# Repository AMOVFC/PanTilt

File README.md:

# Motorized 4-Axis Camera Slider — ESP32-S3

DIY motorized camera slider built around a salvaged 2020 aluminium V-slot
extrusion. Four motorized axes, live knob control, and a programmed keyframe
system for smooth multi-axis cinematic moves. The camera is a phone running the
Blackmagic Camera app; recording is triggered wirelessly over BLE HID.

## Axes

| Axis | Drive | Reduction | Position sensing |
|---|---|---|---|
| Slide | GT2 belt along the 2020 rail, V-wheel carriage | 1:1 | 2× limit switches (min/max) |
| Pan | 2-stage GT2 belt (20T:20T jackshaft, then 20T:80T) | 4:1 | AS5600 absolute encoder — no homing |
| Tilt | Same 2-stage scheme as pan | 4:1 | AS5600 absolute encoder — no homing |
| Z (height) | Integrated leadscrew NEMA 17, anti-backlash nut | 8 mm lead | 1× limit switch, then step-counted |

Pan and tilt read absolute angle on every power-up, so they never need a homing
move. Slide and Z home against physical switches.

## Where things live

| Path | What it is |
|---|---|
| **[`hardware/`](hardware/)** | The production PCB — `pantilt-controller`, a KiCad 10 project. Carrier for an ESP32-S3 DevKitC-1 + 4× TMC2209 sockets + I²C mux + encoders + OLED, with fused inputs and TVS protection on the 24 V / 5 V rails. Board renders, full BOM with LCSC part numbers, and the DFM review scripts are in there. |
| **[`software/`](software/)** | The firmware — a PlatformIO project for the ESP32-S3. Motion, TMC2209 UART control, encoders, sequencer, and a self-hosted web UI. Build and flash from inside `software/`. |
| **[`legacy/`](legacy/)** | Every earlier design generation — nothing the current firmware or board depends on. |

### Legacy generations

| Variant | Path | Why it stopped |
|---|---|---|
| Prototype | [`legacy/prototype/`](legacy/prototype/README.md) | 3-axis hand-wired origin of the project, with its own firmware |
| Integrated | [`legacy/integrated/`](legacy/integrated/README.md) | everything soldered incl. 4× QFN28; never routed |
| Hybrid | [`legacy/hybrid/`](legacy/hybrid/README.md) | soldered MCU + power, plug-in drivers |
| Turnkey / -mini / full / pwr | [`legacy/pantiltslide/`](legacy/pantiltslide/README.md) | earlier carrier boards; `hardware/pantilt-controller` descends from turnkey-mini |
| TMC socket generator | [`legacy/tmc2209-socket-gen/`](legacy/tmc2209-socket-gen/) | script + library for the custom TMC2209 socket footprint |

## The board in one paragraph

An ESP32-S3 DevKitC-1 drops into two 22-pin sockets. Four TMC2209
SilentStepSticks and a TCA9548A breakout plug into pin sockets; two AS5600
encoder heads, four panel encoders, four buttons and the limit switches plug in
over JST-XH; the OLED and the six spare mux channels break out on 1×4 pin
headers. Both supply rails are fused — a 4 A MINI blade fuse on the 24 V motor
rail, a 1.5 A Nano² on the 5 V logic rail — with a TVS crowbar downstream of
each fuse and a bleeder across the 24 V bulk caps so hand-driving an axis while
the board is off can't leave the capacitors charged. Details and BOM:
[`hardware/README.md`](hardware/README.md).

## The firmware in one paragraph

Motion runs on STEP/DIR through FastAccelStepper; the TMC2209s are configured
and health-checked over one shared half-duplex UART, so run current and
microstepping are set by firmware rather than by trimpots and jumpers. Anything
machine-specific — pin map, mechanics, speeds, soft limits, control bindings,
network — is runtime config on the ESP32's filesystem, edited from a web UI
that is compiled into the image. `software/include/config.h` holds factory
defaults only. Bring-up order and bench notes:
[`software/docs/firmware.md`](software/docs/firmware.md).

## Manufacturing

PCBWay fabricate the bare 4-layer PCB. Components are **hand-assembled** —
PCBWay only warranty parts they also place, so the BOM is kept to common,
reusable Uniroyal / Yageo passives and widely-stocked LCSC parts. Motors, PSU,
AS5600 modules, OLED, encoders and mechanical parts wire in over connectors.

## Quick start

```bash
cd software
pio run -t upload && pio device monitor
```

Flash through the DevKitC-1's **`UART`** USB socket (not `USB`). The board then
comes up as a WiFi AP — SSID `CamSlider`, password `sliderpad`, UI at
`http://192.168.4.1`. Full instructions and the mandatory pre-motor bring-up
sequence: [`software/README.md`](software/README.md).

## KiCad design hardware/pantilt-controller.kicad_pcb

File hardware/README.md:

# pantilt-controller — carrier board

The production PCB for the 4-axis camera slider. A carrier for an **ESP32-S3
DevKitC-1** that fans the module out to four **TMC2209 SilentStepStick** driver
sockets, a **TCA9548A** I²C mux, two **AS5600** encoder heads, an OLED, four
quadrature encoders, four buttons and the limit switches — everything on
plug-in connectors — plus on-board power protection on the 24 V and 5 V rails.

Everything that describes a *particular* machine (pin map, mechanics, speeds,
limits) lives in the firmware's runtime config, not on this board. See
[`../software/`](../software/).

|  |  |
|---|---|
|  |  |
| **Top** — every cabled connector (JST-XH, terminal blocks, 1×4 headers for the OLED and spare mux channels), the electrolytics, F1 / F2 and the power LEDs | **Bottom** — the DevKit, TMC2209 and TCA9548A sockets (the modules plug in from underneath), SMD decoupling, I²C pull-ups, TVS diodes |

Renders are `kicad-cli` ray-traces of the board file. F1 and F2 have no 3-D
model and show as bare pads. To regenerate, from this folder:

```bash
kicad-cli pcb render --side top    --rotate "-40,0,35"  --zoom 0.9 --quality high --floor --perspective --background opaque --width 1568 --height 984 --output renders/pantilt-controller-top.png    pantilt-controller.kicad_pcb
kicad-cli pcb render --side bottom --rotate "-40,0,-35" --zoom 0.9 --quality high --floor --perspective --background opaque --width 1568 --height 984 --output renders/pantilt-controller-bottom.png pantilt-controller.kicad_pcb
```

## At a glance

| | |
|---|---|
| Size | 52.3 × 93.2 mm |
| Layers | 4 (1 oz outer + inner) |
| Stackup | `F.Cu` / prepreg 0.1 / `In1.Cu` / core 1.24 / `In2.Cu` / prepreg 0.1 / `B.Cu` ≈ 1.6 mm |
| Planes | `In1.Cu` + `In2.Cu` are both solid GND; F/B carry signal + power |
| Rails | 24 V (motor), 5 V (DevKit + logic), 3.3 V (from the DevKit regulator) |
| DRC | 0 errors, 0 unconnected · 64 warnings, all cosmetic (silkscreen overlap / silk over copper, back-layer text, TMC socket library-copy mismatch) |
| ERC | 0 errors · 96 warnings, mostly off-grid wire endpoints |
| Schematic parity | 30 items — 26 part-field syncs (MPN / LCSC / Notes not yet copied onto the footprints; *Update PCB from Schematic* fixes them without moving anything, since every symbol's footprint matches the board) plus 4 notes on the unnamed `REF**` mounting holes |
| On-silk name | `PanTiltSlide v1.0 · AMOVFC` (silk text predates the `pantilt-controller` project rename) |

## Power and protection

This board is the "mini" carrier **plus** a protection block. Both input rails
are fused, and each has a TVS crowbar downstream of its fuse:

| Ref | Part | Function |
|---|---|---|
| **F1** | XFCN XF-508P-B-B MINI (ATM) blade fuse holder (`C19727305`) with a **4 A** MINI blade fuse (Littelfuse 297/997 or Bussmann ATM — bought separately) | 24 V input fuse |
| **D1** | SMBJ33A uni-directional TVS, cathode→+24 V, anode→GND (`C7427916`) | 24 V crowbar: clamps regen/overvoltage transients; conducts hard on reverse polarity to blow F1 |
| **R29 + R30** | 2 × 10 kΩ in series = 20 kΩ across +24 V / GND | Bleeder — drains the ~870 µF of bulk when the board is off (τ ≈ 17 s), so hand-driving the slide axis can't leave the caps charged. ~29 mW standing. |
| **F2** | Littelfuse 154 OMNI-BLOK 1.5 A slow-blow Nano² fuse **+ holder** assembly (`C206920`) | 5 V input fuse |
| **D2** | SMBJ6.5A uni-directional TVS, cathode→VCC_5V, anode→GND (`C52176732`) | 5 V crowbar, downstream of F2 |
| **LED1 / LED2 / LED3** | red 0805 (Nationstar NCD0805R1, `C84256`) + series R | 24 V / 5 V / 3.3 V present indicators, ≈ 2.2 / 1.4 / 1.4 mA through 10 k / 2.2 k / 1 k. Red's lower forward voltage roughly triples the 3.3 V LED's current compared with the green part it replaced, so all three are clearly visible. |

Bulk capacitance: **C1** 470 µF/50 V at the 24 V fuse output, **C2–C5**
4 × 100 µF/50 V one per driver, **C10** 100 µF/25 V on the 5 V input,
**C12** 22 µF on 3.3 V, plus 100 nF ceramics throughout.

## Connectors

Module sockets are on the bottom; everything that takes a cable is on the top.

| Ref(s) | Label | Type | Goes to |
|---|---|---|---|
| J1, J2 | — | 2 × 22-pin socket, 22.86 mm apart (bottom) | ESP32-S3 DevKitC-1 |
| U1–U4 | tmc2209 | 2 × 1×8 socket each (bottom) | TMC2209 SilentStepStick (pads 17/18 unused) |
| J20, J24 | TCA9548A_Mux | 2 × 12-pin socket (bottom) | TCA9548A breakout |
| J17 / J18 / J19 / J28 | Motor_Slide / Pan / Tilt / Aux | 4-pin JST-XH | stepper coils (A+ A− B+ B−) |
| J21 / J22 | AS5600_Pan / Tilt | 4-pin JST-XH | AS5600 magnet-encoder heads (I²C) |
| J29 / J30 / J31 / J32 | Enc_Slide / Pan / Tilt / Aux | 3-pin JST-XH | panel quadrature encoders |
| J26 / J27 | Limit_Min / Max | 2-pin JST-XH | slide end-stop switches |
| J41 | Aux_Max | 2-pin JST-XH | Z / aux end-stop |
| J33 / J34 / J35 / J36 | Btn_SetKeyframe / ClearKeyframe / PlayPause / Reset | 2-pin JST-XH | panel buttons |
| J23 | OLED | 1×4 male pin header | SSD1306 128×64 I²C OLED |
| J37 / J38 | 5V_In / 24V_In | 5 mm 2-pin terminal block | supplies |
| J3–J8 | MUX_2 … MUX_7 | 1×4 male pin header | breakouts for the 6 spare TCA9548A channels |

Full source→destination GPIO map: [`../software/docs/pinout.md`](../software/docs/pinout.md).

## Bill of materials

Generated from the schematic — [`bom.csv`](bom.csv) is the machine-readable
copy. Grouped by value; `Qty` is total pieces per board. Every LCSC number was
re-checked against LCSC stock and ordered as the build cart on 2026-09-12, and
`bom.csv` and the schematic agree on all 24 parts. The part fields haven't been
copied onto the PCB footprints yet (see *Schematic parity* above).

| Refs | Value | Footprint | Qty | MPN | Mfr | LCSC |
|---|---|---|--:|---|---|---|
| C1 | 470 µF / 50 V | D10 radial, P5.0 | 1 | KM477M050G20RR0VH2FP0 | Chengx | **C34642** |
| C2–C5 | 100 µF / 50 V | D8 radial, P3.5 | 4 | KM107M050F12RR0VH2FP0 | Aishi | **C2749** |
| C6–C9 | 100 nF / 50 V | 0805 | 4 | CC0805KRX7R9BB104 | Yageo | **C49678** |
| C10 | 100 µF / 25 V | D6.3 radial, P2.5 | 1 | KS107M025E07RR0VH2FP0 | Aishi | **C44587** |
| C11, C13–C20 | 100 nF | 0805 | 9 | CC0805KRX7R9BB104 | Yageo | **C49678** |
| C12 | 22 µF / 16 V | 0805 | 1 | HGC0805R5226K160NSLJ | HGC | **C7472967** |
| D1 | SMBJ33A TVS | SMB | 1 | SMBJ33A | NH | **C7427916** |
| D2 | SMBJ6.5A TVS | SMB | 1 | SMBJ6.5A | TDSEMIC | **C52176732** |
| F1 | 4 A MINI blade fuse holder | XF-508P-B-B | 1 | XF-508P-B-B | XFCN | **C19727305** *(fuse bought separately)* |
| F2 | 1.5 A slow-blow + holder | OMNI-BLOK | 1 | 015401.5DR | Littelfuse | **C206920** |
| J1, J2 | 1×22 socket | PinSocket 2.54 | 2 | ZX-PM2.54-1-22PY | Ckmtw | **C7499337** |
| J20, J24 | 1×12 socket | PinSocket 2.54 | 2 | KH-2.54FH-1X12P-H8.5 | Ckmtw | **C2905419** |
| J3–J8, J23 | 1×4 male pin header | PinSocket 2.54 | 7 | PZ2.54-1X4P-H25 | JXTCONN | **C42431787** |
| J17–J19, J28 | 4-pin | JST-XH B4B | 4 | B4B-XH-A(LF)(SN) | JST | **C144395** |
| J21, J22 | 4-pin | JST-XH B4B | 2 | B4B-XH-A(LF)(SN) | JST | **C144395** |
| J29–J32 | 3-pin | JST-XH B3B | 4 | B3B-XH-A(LF)(SN) | JST | **C144394** |
| J26, J27, J33–J36, J41 | 2-pin | JST-XH B2B | 7 | B2B-XH-A(LF)(SN) | JST | **C158012** |
| J37, J38 | 2-pin terminal, 5 mm | MX126-5.0 | 2 | MX126-5.0-02P-GN01-Cu-S-A | MaiXu | **C5188434** |
| LED1–LED3 | red 0805 | 0805 | 3 | NCD0805R1 | Nationstar | **C84256** |
| R1–R4 | 4.7 kΩ | 0805 | 4 | 0805W8F4701T5E | Uniroyal | **C17673** |
| R5–R8, R32 | 2.2 kΩ | 0805 | 5 | 0805W8F2201T5E | Uniroyal | **C17520** |
| R10, R11 | 100 Ω | 0603 | 2 | 0603WAF1000T5E | Uniroyal | **C22775** |
| R12 | 1 kΩ | 0603 | 1 | 0603WAF1001T5E | Uniroyal | **C21190** |
| R25–R31 | 10 kΩ | 0805 | 7 | 0805W8F1002T5E | Uniroyal | **C17414** |
| R33 | 1 kΩ | 0805 | 1 | 0805W8F1001T5E | Uniroyal | **C17513** |
| U1–U4 | TMC2209 socket | 2 × 1×8, 2.54 | 4 | 2.54-1×8P | Ckmtw | **C27438** |

**Not on the LCSC BOM** — bought separately or supplied by the builder:
ESP32-S3 DevKitC-1, 4 × TMC2209 SilentStepStick, TCA9548A breakout, 2 × AS5600
module, SSD1306 OLED, 4 × panel encoder, 4 × panel button, limit switches,
steppers, 24 V PSU, and the 4 A MINI blade fuse for F1.

> R1–R4 (4.7 k) and R5–R8 (2.2 k) are the I²C pull-ups — bus A / the two active
> mux channels. J3–J8 and J23 take male 1×4 headers in `PinSocket_1x04`
> footprints: the copper is identical (2.54 mm pitch, Ø1.0 mm drill), and the
> header's datasheet recommends Ø1.02 mm for its 0.64 mm square pins.

## Manufacturing

1. **Fab the bare PCB** at PCBWay (or any 4-layer house) — standard 1.6 mm,
   1 oz, HASL/ENIG, from the Gerbers you plot out of KiCad. **Refill zones
   (`B`) and save before plotting** — the Gerbers carry whatever copper pour is
   stored in the file, and a stale pour can sit inside the clearance of a part
   that has moved.
2. **Hand-assemble** from the LCSC cart above. PCBWay only warranty parts they
   also place, so the BOM deliberately sticks to common Uniroyal / Yageo
   passives and stocked LCSC parts that are useful on other projects too.
   F1's four holes are drilled Ø1.6 mm, the XFCN datasheet minimum; the
   holder's 0.40 × 1.60 mm flat pins measure 1.65 mm across the diagonal, so
   expect a tight fit — a 1.7 mm reamer opens the holes if it won't seat.
3. [`fp-lib-table`](fp-lib-table) registers the project's `PanTilt` (F1
   holder) and `TMC2209` libraries. U1–U4 still report
   `lib_footprint_mismatch` — the board's embedded socket differs from
   `lib/TMC2209.pretty` — which doesn't affect the Gerbers. The TMC socket's
   courtyard is also malformed in that third-party footprint;
   `malformed_courtyard` is set to *ignore* to match the older boards.

## Folder contents

```
pantilt-controller.kicad_{pcb,sch,pro,prl}   the KiCad 10 project
fp-lib-table                                  registers lib/PanTilt.pretty and lib/TMC2209.pretty
bom.csv                                       BOM export (regenerate with kicad-cli sch export bom)
renders/                                      board renders (kicad-cli pcb render — command above)
lib/PanTilt.pretty                            F1 fuse-holder footprint (XFCN XF-508P-B-B)
lib/TMC2209.pretty, lib/New_Library.kicad_sym the board's TMC socket footprint / symbol deps
tools/pcb_review/                             deterministic DFM review scripts (used by .github/workflows/pcb-review.yml)
```

See the repo root [`README.md`](../README.md) for the project overview and
[`../legacy/`](../legacy/) for the earlier board generations.

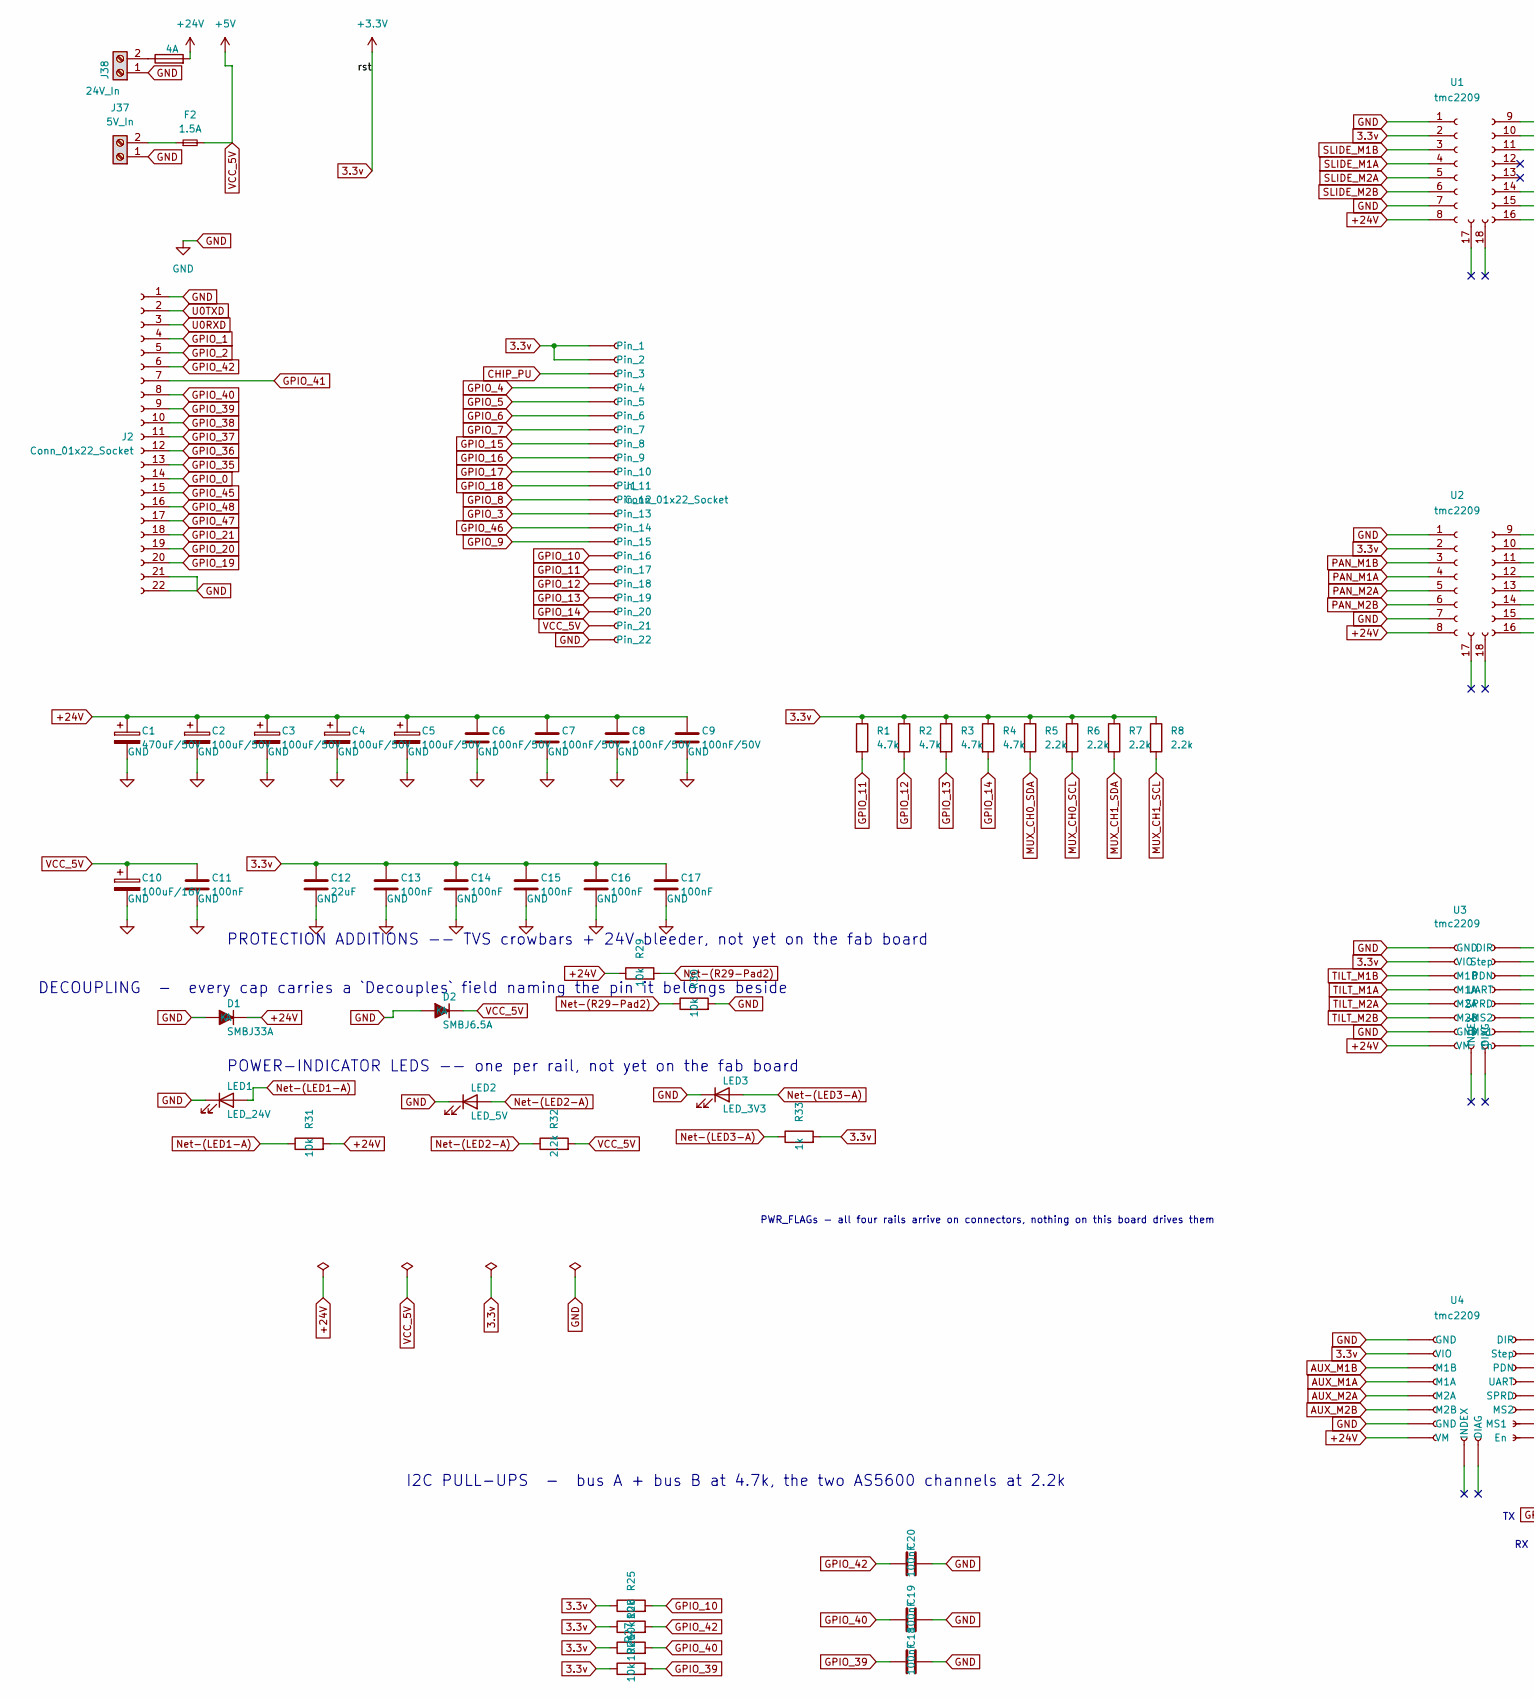
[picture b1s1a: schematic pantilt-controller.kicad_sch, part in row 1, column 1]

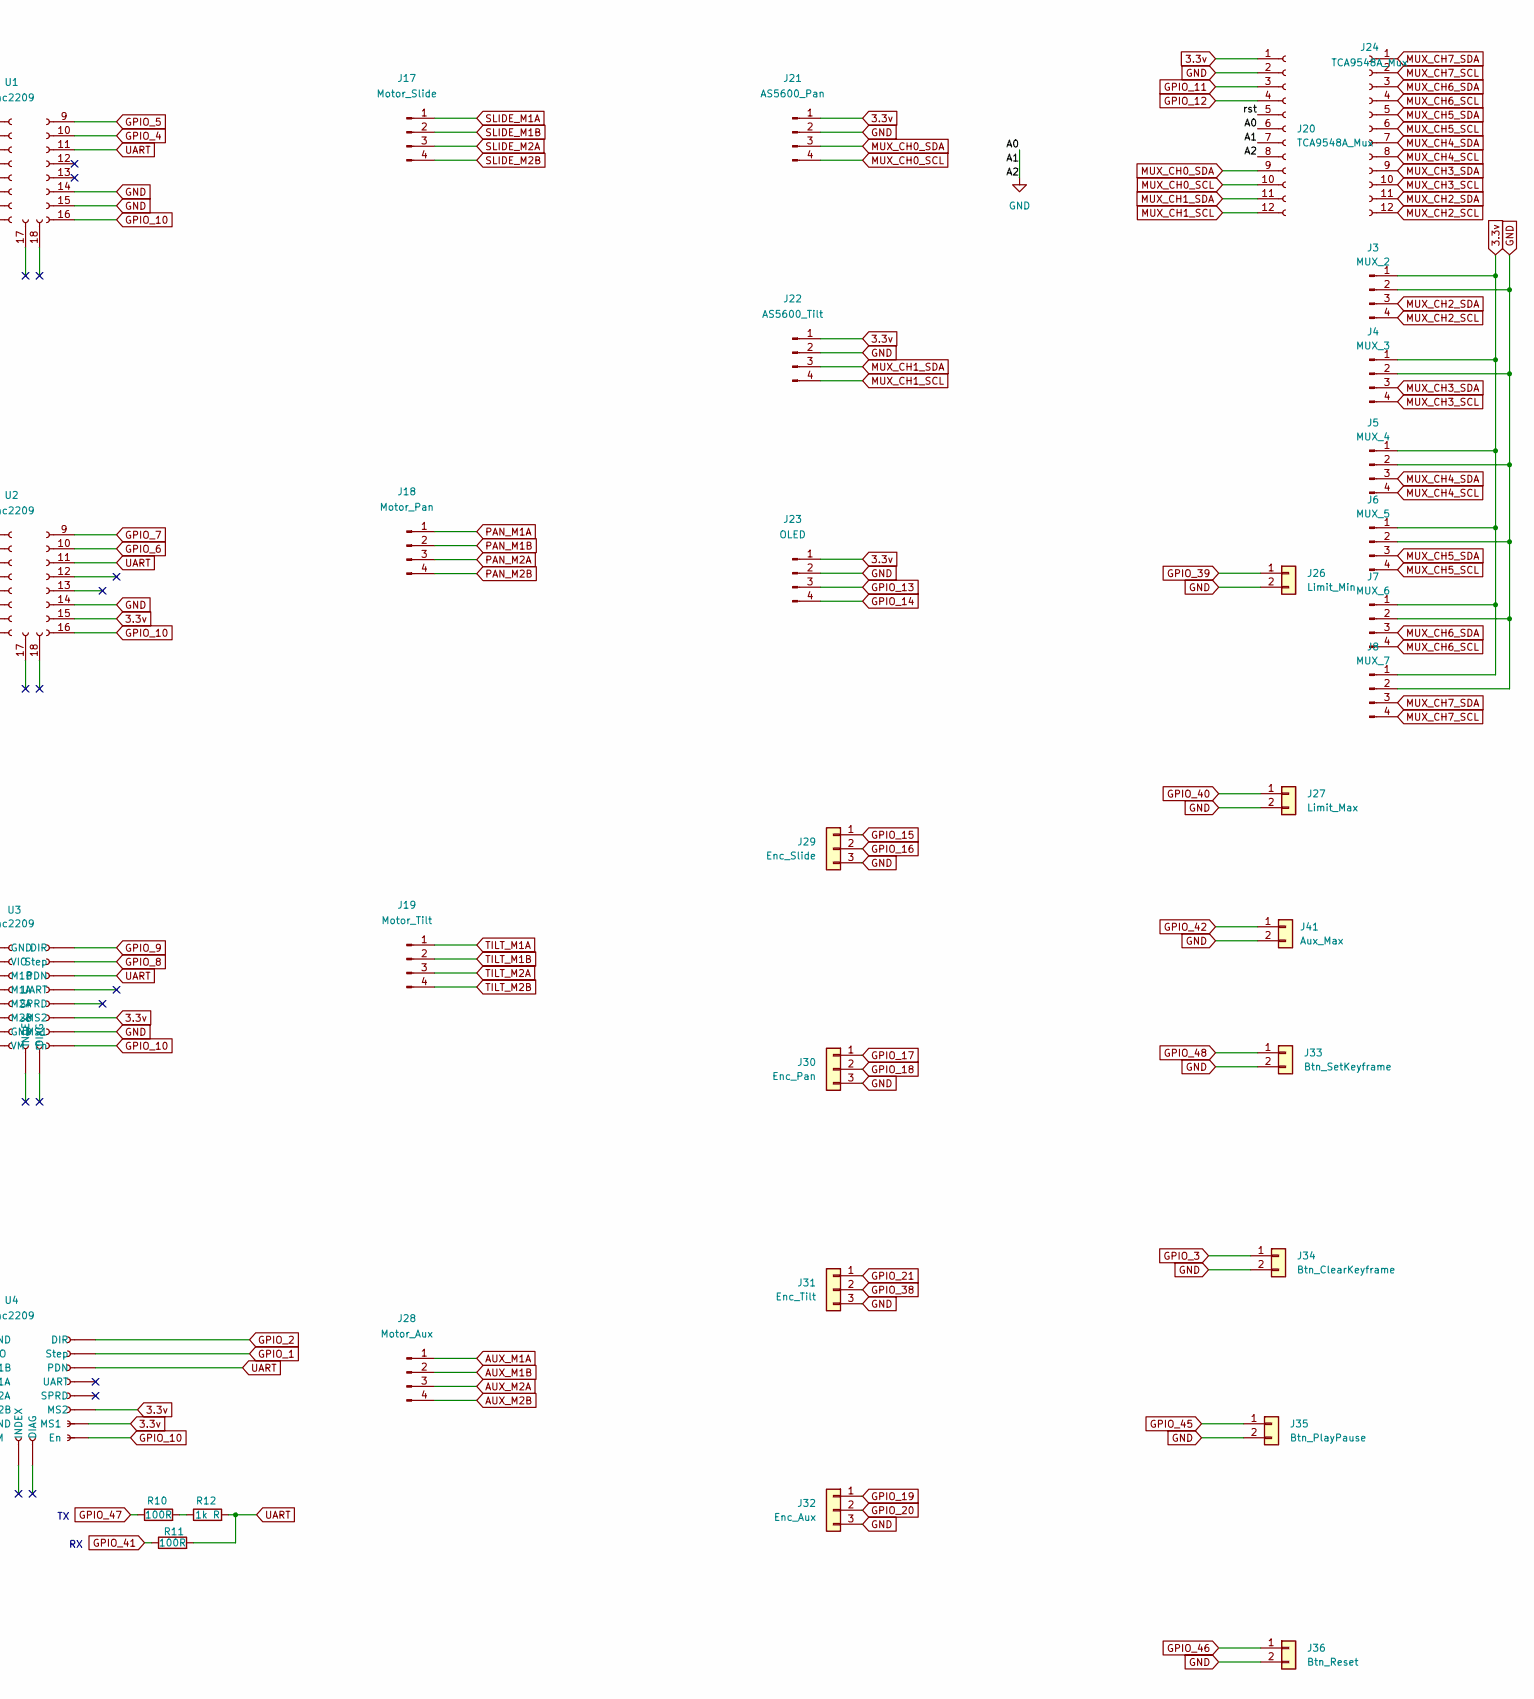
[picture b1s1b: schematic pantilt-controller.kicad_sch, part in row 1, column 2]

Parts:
C1: 470uF/50V; CP_Radial_D10.0mm_P5.00mm; MPN KM477M050G20RR0VH2FP0; LCSC C34642
C2, C3, C4, C5: 100uF/50V; CP_Radial_D8.0mm_P3.50mm; MPN KM107M050F12RR0VH2FP0; LCSC C2749
C6, C7, C8, C9: 100nF/50V; C_0805_2012Metric; MPN CC0805KRX7R9BB104; LCSC C49678
C10: 100uF/16V; CP_Radial_D6.3mm_P2.50mm; MPN KS107M025E07RR0VH2FP0; LCSC C44587
C11, C13, C14, C15, C16, C17, C18, C19, C20: 100nF; C_0805_2012Metric; MPN CC0805KRX7R9BB104; LCSC C49678
C12: 22uF; C_0805_2012Metric; MPN HGC0805R5226K160NSLJ; LCSC C7472967
D1: SMBJ33A; D_SMB; MPN SMBJ33A; LCSC C7427916
D2: SMBJ6.5A; D_SMB; MPN SMBJ6.5A; LCSC C52176732
F1: 4A; Fuseholder_Blade_Mini_XFCN_XF-508P-B-B; MPN XF-508P-B-B; LCSC C19727305
F2: 1.5A; NANO-0154-OMNI-BLOK-Fuse-Holder; MPN 015401.5DR; LCSC C206920
J1, J2: Conn_01x22_Socket; PinSocket_1x22_P2.54mm_Vertical; MPN ZX-PM2.54-1-22PY; LCSC C7499337
J3: MUX_2
J4: MUX_3
J5: MUX_4
J6: MUX_5
J7: MUX_6
J8: MUX_7
J17: Motor_Slide; JST_XH_B4B-XH-A_1x04_P2.50mm_Vertical; MPN B4B-XH-A(LF)(SN); LCSC C144395
J18: Motor_Pan; JST_XH_B4B-XH-A_1x04_P2.50mm_Vertical; MPN B4B-XH-A(LF)(SN); LCSC C144395
J19: Motor_Tilt; JST_XH_B4B-XH-A_1x04_P2.50mm_Vertical; MPN B4B-XH-A(LF)(SN); LCSC C144395
J20, J24: TCA9548A_Mux; PinSocket_1x12_P2.54mm_Vertical; MPN KH-2.54FH-1X12P-H8.5; LCSC C2905419
J21: AS5600_Pan; JST_XH_B4B-XH-A_1x04_P2.50mm_Vertical; MPN B4B-XH-A(LF)(SN); LCSC C144395
J22: AS5600_Tilt; JST_XH_B4B-XH-A_1x04_P2.50mm_Vertical; MPN B4B-XH-A(LF)(SN); LCSC C144395
J23: OLED; PinSocket_1x04_P2.54mm_Vertical; MPN 2.54-1*4P; LCSC C2718488
J26: Limit_Min; JST_XH_B2B-XH-A_1x02_P2.50mm_Vertical; MPN B2B-XH-A(LF)(SN); LCSC C158012
J27: Limit_Max; JST_XH_B2B-XH-A_1x02_P2.50mm_Vertical; MPN B2B-XH-A(LF)(SN); LCSC C158012
J28: Motor_Aux; JST_XH_B4B-XH-A_1x04_P2.50mm_Vertical; MPN B4B-XH-A(LF)(SN); LCSC C144395
J29: Enc_Slide; JST_XH_B3B-XH-A_1x03_P2.50mm_Vertical; MPN B3B-XH-A(LF)(SN); LCSC C144394
J30: Enc_Pan; JST_XH_B3B-XH-A_1x03_P2.50mm_Vertical; MPN B3B-XH-A(LF)(SN); LCSC C144394
J31: Enc_Tilt; JST_XH_B3B-XH-A_1x03_P2.50mm_Vertical; MPN B3B-XH-A(LF)(SN); LCSC C144394
J32: Enc_Aux; JST_XH_B3B-XH-A_1x03_P2.50mm_Vertical; MPN B3B-XH-A(LF)(SN); LCSC C144394
J33: Btn_SetKeyframe; JST_XH_B2B-XH-A_1x02_P2.50mm_Vertical; MPN B2B-XH-A(LF)(SN); LCSC C158012
J34: Btn_ClearKeyframe; JST_XH_B2B-XH-A_1x02_P2.50mm_Vertical; MPN B2B-XH-A(LF)(SN); LCSC C158012
J35: Btn_PlayPause; JST_XH_B2B-XH-A_1x02_P2.50mm_Vertical; MPN B2B-XH-A(LF)(SN); LCSC C158012
J36: Btn_Reset; JST_XH_B2B-XH-A_1x02_P2.50mm_Vertical; MPN B2B-XH-A(LF)(SN); LCSC C158012
J37: 5V_In; TerminalBlock_MaiXu_MX126-5.0-02P_1x02_P5.00mm; MPN MX126-5.0-02P-GN01-Cu-S-A; LCSC C5188434
J38: 24V_In; TerminalBlock_MaiXu_MX126-5.0-02P_1x02_P5.00mm; MPN MX126-5.0-02P-GN01-Cu-S-A; LCSC C5188434
J41: Aux_Max; JST_XH_B2B-XH-A_1x02_P2.50mm_Vertical; MPN B2B-XH-A(LF)(SN); LCSC C158012
LED1: LED_24V; LED_0805_2012Metric; MPN NCD0805R1; LCSC C84256
LED2: LED_5V; LED_0805_2012Metric; MPN NCD0805R1; LCSC C84256
LED3: LED_3V3; LED_0805_2012Metric; MPN NCD0805R1; LCSC C84256
R1, R2, R3, R4: 4.7k; R_0805_2012Metric; MPN 0805W8F4701T5E; LCSC C17673
R5, R6, R7, R8, R32: 2.2k; R_0805_2012Metric; MPN 0805W8F2201T5E; LCSC C17520
R10, R11: 100R; R_0603_1608Metric; MPN 0603WAF1000T5E; LCSC C22775
R12: 1k R; R_0603_1608Metric; MPN 0603WAF1001T5E; LCSC C21190
R25, R26, R27, R28, R29, R30, R31: 10k; R_0805_2012Metric; MPN 0805W8F1002T5E; LCSC C17414
R33: 1k; R_0805_2012Metric; MPN 0805W8F1001T5E; LCSC C17513
U1, U2, U3: tmc2209; TMC2209_SilentStepStick_Socket_18P; MPN 2.54-1*8P; LCSC C27438
U4: tmc2209; MPN 2.54-1*8P; LCSC C27438

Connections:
3.3v: C12.1, C13.1, C14.1, C15.1, C16.1, C17.1, J1.1, J1.2, J3.1, J4.1, J5.1, J6.1, J7.1, J8.1, J20.1, J20.5, J21.1, J22.1, J23.1, R1.1, R2.1, R3.1, R4.1, R5.1, R6.1, R7.1, R8.1, R25.1, R26.1, R27.1, R28.1, R33.2, U1.2 (VIO), U2.2 (VIO), U2.15 (MS1), U3.2 (VIO), U3.14 (MS2), U4.2 (VIO), U4.14 (MS2), U4.15 (MS1)
+24V: C1.1, C2.1, C3.1, C4.1, C5.1, C6.1, C7.1, C8.1, C9.1, D1.2 (K), F1.2, R29.1, R31.2, U1.8 (VM), U2.8 (VM), U3.8 (VM), U4.8 (VM)
AUX_M1A: J28.1, U4.4 (M1A)
AUX_M1B: J28.2, U4.3 (M1B)
AUX_M2A: J28.3, U4.5 (M2A)
AUX_M2B: J28.4, U4.6 (M2B)
CHIP_PU: J1.3
GND: C1.2, C2.2, C3.2, C4.2, C5.2, C6.2, C7.2, C8.2, C9.2, C10.2, C11.2, C12.2, C13.2, C14.2, C15.2, C16.2, C17.2, C18.2, C19.2, C20.2, D1.1 (A), D2.1 (A), J1.22, J2.1, J2.21, J2.22, J3.2, J4.2, J5.2, J6.2, J7.2, J8.2, J20.2, J20.6, J20.7, J20.8, J21.2, J22.2, J23.2, J26.2, J27.2, J29.3, J30.3, J31.3, J32.3, J33.2, J34.2, J35.2, J36.2, J37.1, J38.1, J41.2, LED1.1 (K), LED2.1 (K), LED3.1 (K), R30.2, U1.1 (GND), U1.7 (GND), U1.14 (MS2), U1.15 (MS1), U2.1 (GND), U2.7 (GND), U2.14 (MS2), U3.1 (GND), U3.7 (GND), U3.15 (MS1), U4.1 (GND), U4.7 (GND)
GPIO_0: J2.14
GPIO_1: J2.4, U4.10 (Step)
GPIO_2: J2.5, U4.9 (DIR)
GPIO_3: J1.13, J34.1
GPIO_4: J1.4, U1.10 (Step)
GPIO_5: J1.5, U1.9 (DIR)
GPIO_6: J1.6, U2.10 (Step)
GPIO_7: J1.7, U2.9 (DIR)
GPIO_8: J1.12, U3.10 (Step)
GPIO_9: J1.15, U3.9 (DIR)
GPIO_10: J1.16, R25.2, U1.16 (En), U2.16 (En), U3.16 (En), U4.16 (En)
GPIO_11: J1.17, J20.3, R1.2
GPIO_12: J1.18, J20.4, R2.2
GPIO_13: J1.19, J23.3, R3.2
GPIO_14: J1.20, J23.4, R4.2
GPIO_15: J1.8, J29.1
GPIO_16: J1.9, J29.2
GPIO_17: J1.10, J30.1
GPIO_18: J1.11, J30.2
GPIO_19: J2.20, J32.1
GPIO_20: J2.19, J32.2
GPIO_21: J2.18, J31.1
GPIO_35: J2.13
GPIO_36: J2.12
GPIO_37: J2.11
GPIO_38: J2.10, J31.2
GPIO_39: C18.1, J2.9, J26.1, R26.2
GPIO_40: C19.1, J2.8, J27.1, R27.2
GPIO_41: J2.7, R11.1
GPIO_42: C20.1, J2.6, J41.1, R28.2
GPIO_45: J2.15, J35.1
GPIO_46: J1.14, J36.1
GPIO_47: J2.17, R10.1
GPIO_48: J2.16, J33.1
MUX_CH0_SCL: J20.10, J21.4, R6.2
MUX_CH0_SDA: J20.9, J21.3, R5.2
MUX_CH1_SCL: J20.12, J22.4, R8.2
MUX_CH1_SDA: J20.11, J22.3, R7.2
MUX_CH2_SCL: J3.4, J24.12
MUX_CH2_SDA: J3.3, J24.11
MUX_CH3_SCL: J4.4, J24.10
MUX_CH3_SDA: J4.3, J24.9
MUX_CH4_SCL: J5.4, J24.8
MUX_CH4_SDA: J5.3, J24.7
MUX_CH5_SCL: J6.4, J24.6
MUX_CH5_SDA: J6.3, J24.5
MUX_CH6_SCL: J7.4, J24.4
MUX_CH6_SDA: J7.3, J24.3
MUX_CH7_SCL: J8.4, J24.2
MUX_CH7_SDA: J8.3, J24.1
unnamed: F2.1, J37.2
unnamed: F1.1, J38.2
unnamed: LED1.2 (A), R31.1
unnamed: LED2.2 (A), R32.1
unnamed: LED3.2 (A), R33.1
unnamed: R10.2, R12.1
unnamed: R29.2, R30.1
PAN_M1A: J18.1, U2.4 (M1A)
PAN_M1B: J18.2, U2.3 (M1B)
PAN_M2A: J18.3, U2.5 (M2A)
PAN_M2B: J18.4, U2.6 (M2B)
SLIDE_M1A: J17.1, U1.4 (M1A)
SLIDE_M1B: J17.2, U1.3 (M1B)
SLIDE_M2A: J17.3, U1.5 (M2A)
SLIDE_M2B: J17.4, U1.6 (M2B)
TILT_M1A: J19.1, U3.4 (M1A)
TILT_M1B: J19.2, U3.3 (M1B)
TILT_M2A: J19.3, U3.5 (M2A)
TILT_M2B: J19.4, U3.6 (M2B)
U0RXD: J2.3
U0TXD: J2.2
UART: R11.2, R12.2, U1.11 (PDN), U2.11 (PDN), U3.11 (PDN), U4.11 (PDN)
VCC_5V: C10.1, C11.1, D2.2 (K), F2.2, J1.21, R32.2

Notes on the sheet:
DECOUPLING - every cap carries a `Decouples` field naming the pin it belongs beside
PROTECTION ADDITIONS -- TVS crowbars + 24V bleeder, not yet on the fab board
I2C PULL-UPS - bus A + bus B at 4.7k, the two AS5600 channels at 2.2k
PWR_FLAGs - all four rails arrive on connectors, nothing on this board drives them
POWER-INDICATOR LEDS -- one per rail, not yet on the fab board

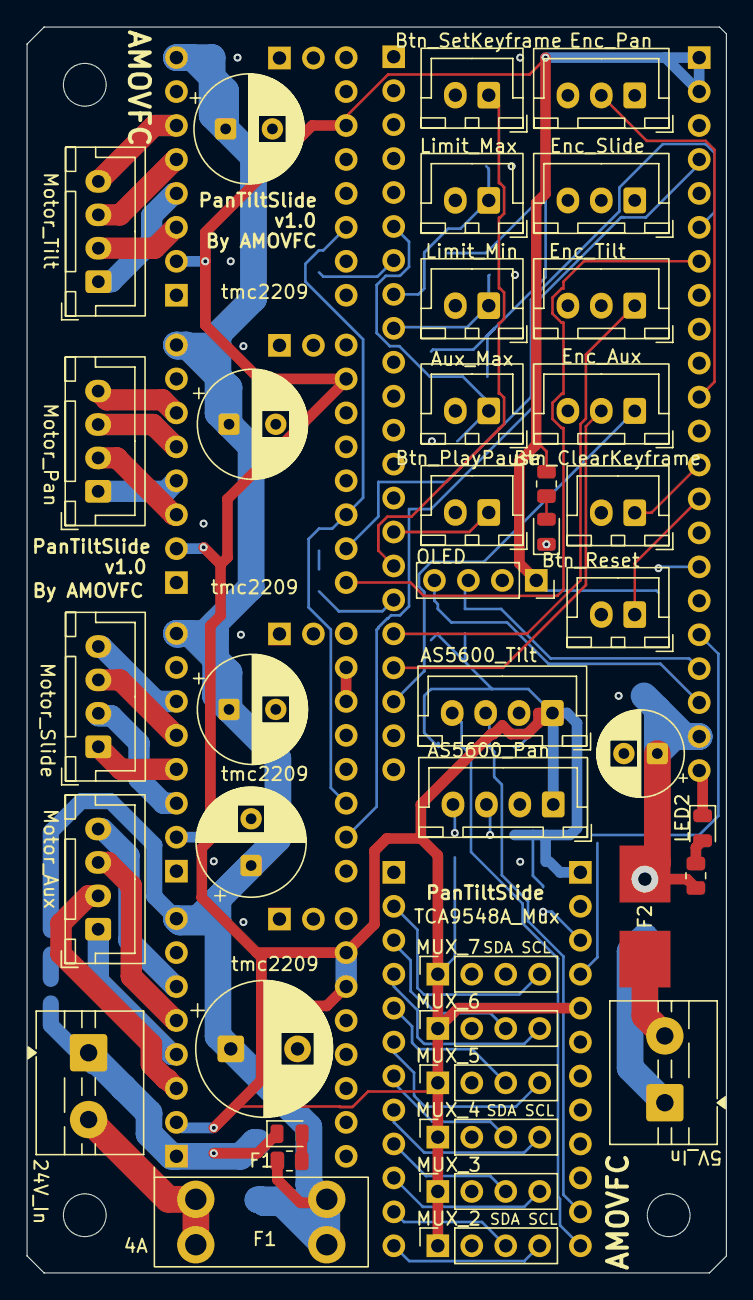
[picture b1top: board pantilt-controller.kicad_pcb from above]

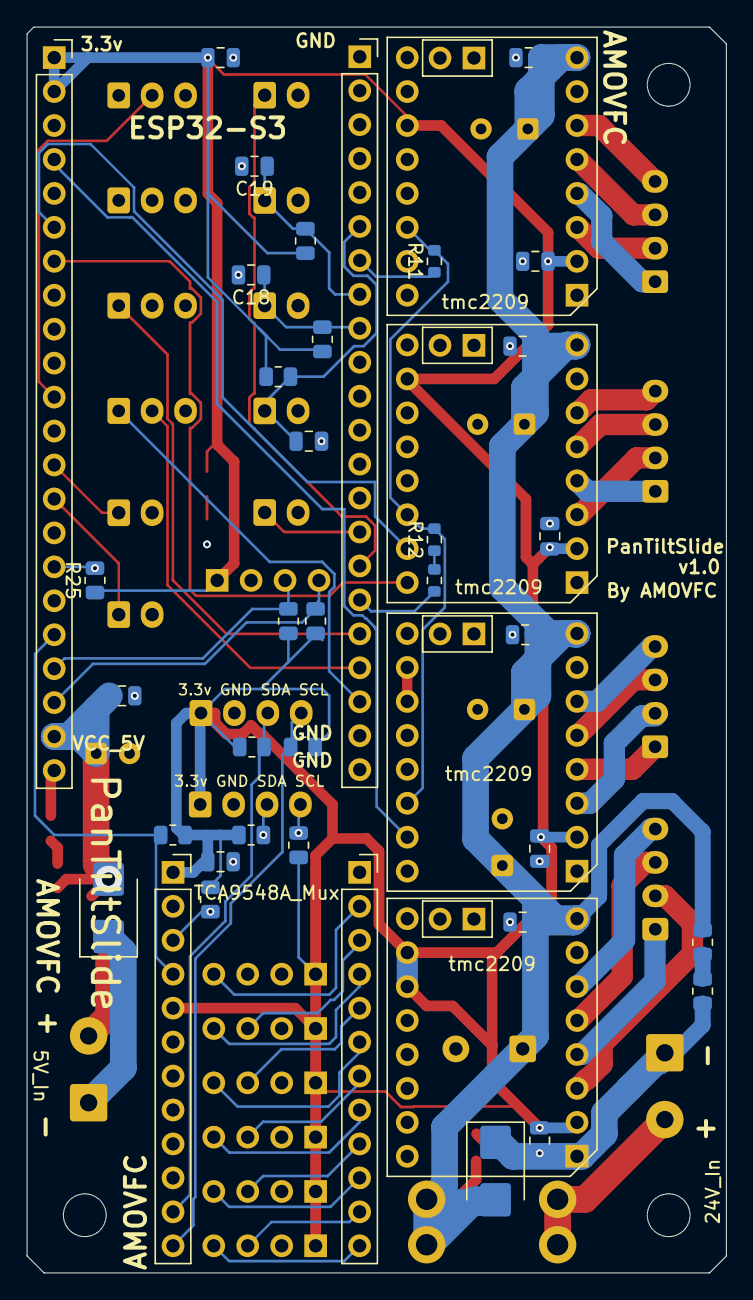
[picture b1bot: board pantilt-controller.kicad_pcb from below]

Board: 4 copper layers, 52.3 x 93.2 mm, 81 parts (41 on the bottom side), 74 nets.

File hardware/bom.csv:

"Refs","Value","Qty","MPN","Mfr","LCSC"
"C1","470uF/50V","1","KM477M050G20RR0VH2FP0","Chengx","C34642"
"C2-C5","100uF/50V","4","KM107M050F12RR0VH2FP0","Aishi","C2749"
"C6-C9","100nF/50V","4","CC0805KRX7R9BB104","Yageo","C49678"
"C10","100uF/16V","1","KS107M025E07RR0VH2FP0","Aishi","C44587"
"C11,C13-C20","100nF","9","CC0805KRX7R9BB104","Yageo","C49678"
"C12","22uF","1","HGC0805R5226K160NSLJ","HGC","C7472967"
"D1","SMBJ33A","1","SMBJ33A","NH","C7427916"
"D2","SMBJ6.5A","1","SMBJ6.5A","TDSEMIC","C52176732"
"F1","4A","1","XF-508P-B-B","XFCN","C19727305"
"F2","1.5A","1","015401.5DR","Littelfuse","C206920"
"J1,J2","Conn_01x22_Socket","2","ZX-PM2.54-1-22PY","Ckmtw","C7499337"
"J3","MUX_2","1","","",""
"J4","MUX_3","1","","",""
"J5","MUX_4","1","","",""
"J6","MUX_5","1","","",""
"J7","MUX_6","1","","",""
"J8","MUX_7","1","","",""
"J17","Motor_Slide","1","B4B-XH-A(LF)(SN)","JST","C144395"
"J18","Motor_Pan","1","B4B-XH-A(LF)(SN)","JST","C144395"
"J19","Motor_Tilt","1","B4B-XH-A(LF)(SN)","JST","C144395"
"J20,J24","TCA9548A_Mux","2","KH-2.54FH-1X12P-H8.5","Ckmtw","C2905419"
"J21","AS5600_Pan","1","B4B-XH-A(LF)(SN)","JST","C144395"
"J22","AS5600_Tilt","1","B4B-XH-A(LF)(SN)","JST","C144395"
"J23","OLED","1","2.54-1*4P","Ckmtw","C2718488"
"J26","Limit_Min","1","B2B-XH-A(LF)(SN)","JST","C158012"
"J27","Limit_Max","1","B2B-XH-A(LF)(SN)","JST","C158012"
"J28","Motor_Aux","1","B4B-XH-A(LF)(SN)","JST","C144395"
"J29","Enc_Slide","1","B3B-XH-A(LF)(SN)","JST","C144394"
"J30","Enc_Pan","1","B3B-XH-A(LF)(SN)","JST","C144394"
"J31","Enc_Tilt","1","B3B-XH-A(LF)(SN)","JST","C144394"
"J32","Enc_Aux","1","B3B-XH-A(LF)(SN)","JST","C144394"
"J33","Btn_SetKeyframe","1","B2B-XH-A(LF)(SN)","JST","C158012"
"J34","Btn_ClearKeyframe","1","B2B-XH-A(LF)(SN)","JST","C158012"
"J35","Btn_PlayPause","1","B2B-XH-A(LF)(SN)","JST","C158012"
"J36","Btn_Reset","1","B2B-XH-A(LF)(SN)","JST","C158012"
"J37","5V_In","1","MX126-5.0-02P-GN01-Cu-S-A","MaiXu","C5188434"
"J38","24V_In","1","MX126-5.0-02P-GN01-Cu-S-A","MaiXu","C5188434"
"J41","Aux_Max","1","B2B-XH-A(LF)(SN)","JST","C158012"
"LED1","LED_24V","1","NCD0805R1","Nationstar","C84256"
"LED2","LED_5V","1","NCD0805R1","Nationstar","C84256"
"LED3","LED_3V3","1","NCD0805R1","Nationstar","C84256"
"R1-R4","4.7k","4","0805W8F4701T5E","Uniroyal","C17673"
"R5-R8,R32","2.2k","5","0805W8F2201T5E","Uniroyal","C17520"
"R10,R11","100R","2","0603WAF1000T5E","Uniroyal","C22775"
"R12","1k R","1","0603WAF1001T5E","Uniroyal","C21190"
"R25-R31","10k","7","0805W8F1002T5E","Uniroyal","C17414"
"R33","1k","1","0805W8F1001T5E","Uniroyal","C17513"
"U1-U4","tmc2209","4","2.54-1*8P","Ckmtw","C27438"
